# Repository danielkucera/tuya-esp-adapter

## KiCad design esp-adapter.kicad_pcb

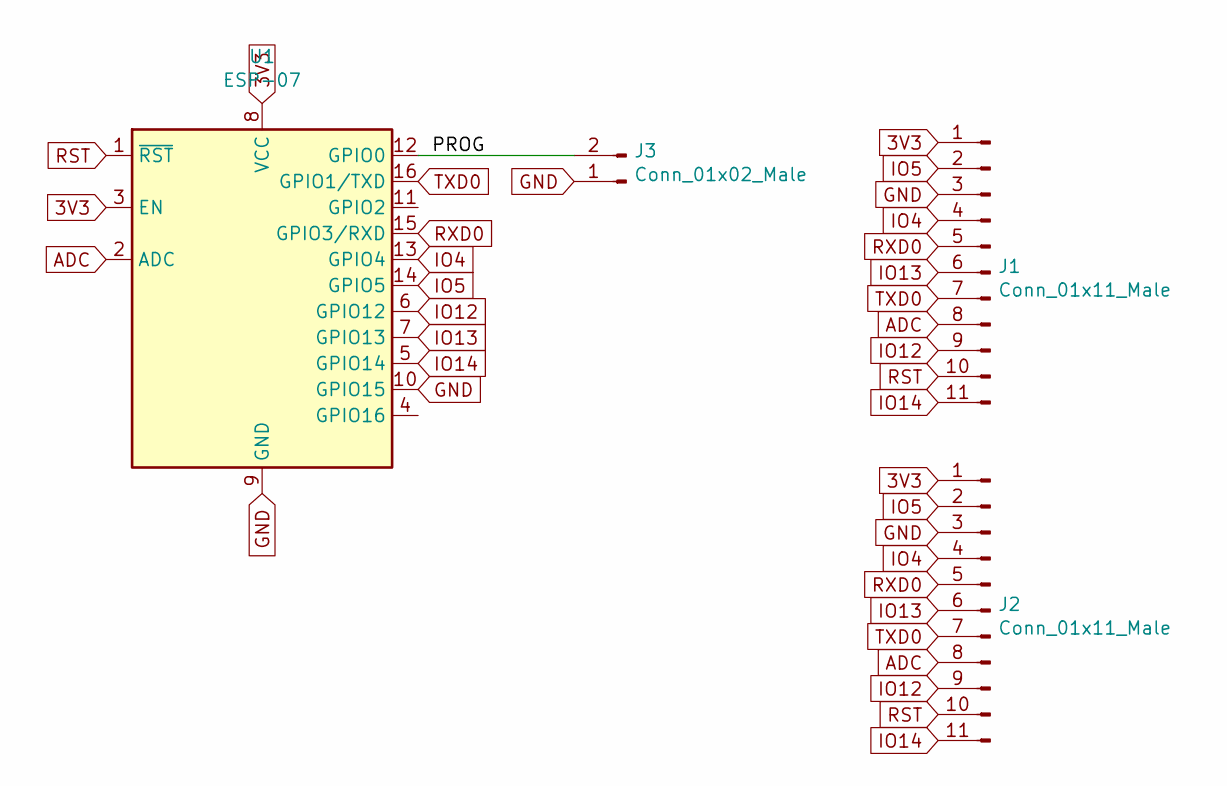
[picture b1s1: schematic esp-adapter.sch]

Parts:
J1: Conn_01x11_Male; edge-conn
J2: Conn_01x11_Male; PinHeader_1x11_P1.00mm_Vertical
J3: Conn_01x02_Male; PinHeader_1x02_P1.27mm_Vertical
U1: ESP-07

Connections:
3V3: J1.1, J2.1, U1.3 (EN), U1.8 (VCC)
/PROG: J3.2, U1.12 (GPIO0)
ADC: J1.8, J2.8, U1.2 (ADC)
GND: J1.3, J2.3, J3.1, U1.9 (GND), U1.10 (GPIO15)
IO4: J1.4, J2.4, U1.13 (GPIO4)
IO5: J1.2, J2.2, U1.14 (GPIO5)
IO12: J1.9, J2.9, U1.6 (GPIO12)
IO13: J1.6, J2.6, U1.7 (GPIO13)
IO14: J1.11, J2.11, U1.5 (GPIO14)
RST: J1.10, J2.10, U1.1 (~RST)
RXD0: J1.5, J2.5, U1.15 (GPIO3/RXD)
TXD0: J1.7, J2.7, U1.16 (GPIO1/TXD)

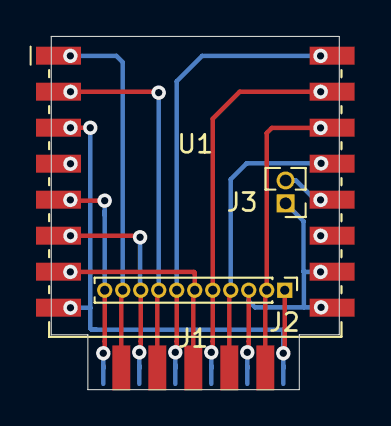
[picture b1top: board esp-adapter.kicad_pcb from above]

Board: 2 copper layers, 16.0 x 19.6 mm, 4 parts (0 on the bottom side), 12 nets.

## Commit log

2021-07-07 intial commit
2021-08-03 thickness 1.0
2021-08-03 no castelated holes
2021-09-08 fabricated version
2021-09-08 fix TX RX swap
2022-01-03 Revert "fix TX RX swap"
    This reverts commit 031c61bf6d1d21104408cedd763a9be0f04462ce.
    For explanation see issue #2 .
